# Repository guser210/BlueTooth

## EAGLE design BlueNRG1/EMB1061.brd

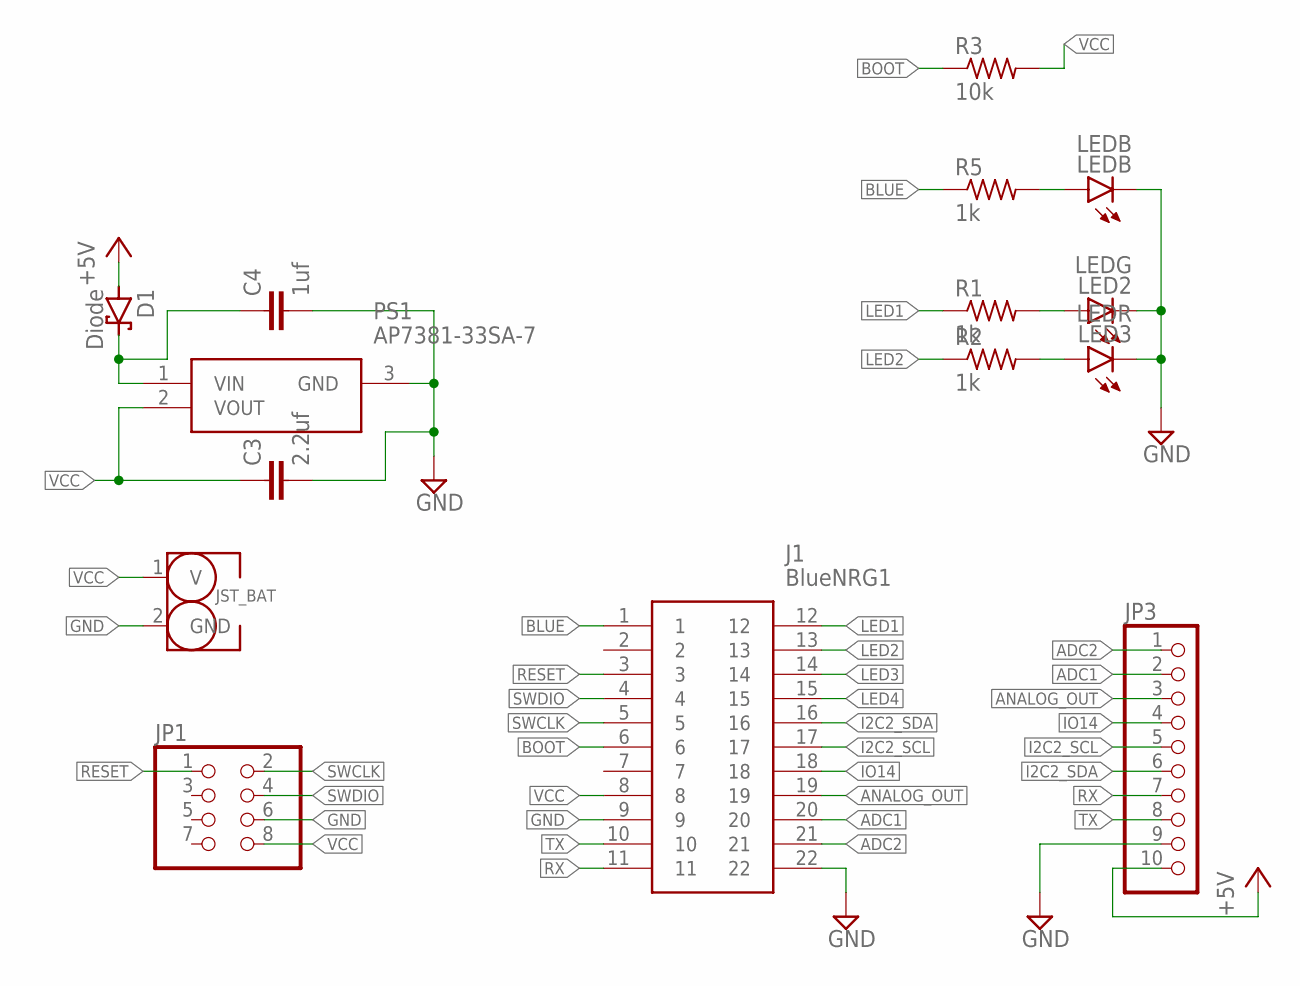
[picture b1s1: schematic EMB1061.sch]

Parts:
C3: 2.2uf; C0603K
C4: 1uf; C0603K
D1: Diode; SOD323_ST
J1: BlueNRG1; 113990637
JP1: PINHD-2X4; 2X04
JP3: PINHD-1X10; 1X10
LED2: LEDG; SML0805
LED3: LEDR; SML0805
LEDB: LEDB; SML0805
PS1: AP7381-33SA-7; SOT96P240X120-3N
R1, R2, R5: 1k; R0805
R3: 10k; R0603
U$1: JST2.0MM_2PIN

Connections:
+5V: D1.A, JP3.10
ADC1: J1.20, JP3.2
ADC2: J1.21, JP3.1
ANALOG_OUT: J1.19, JP3.3
BLUE: J1.1, R5.1
BOOT: J1.6, R3.1
GND: C3.2, C4.2, J1.9, J1.22, JP1.6, JP3.9, LED2.C, LED3.C, LEDB.C, PS1.3 (GND), U$1.2 (GND)
I2C2_SCL: J1.17, JP3.5
I2C2_SDA: J1.16, JP3.6
IO14: J1.18, JP3.4
LED1: J1.12, R1.1
LED2: J1.13, R2.1
LED3: J1.14
LED4: J1.15
unnamed: LEDB.A, R5.2
unnamed: LED2.A, R1.2
unnamed: LED3.A, R2.2
RESET: J1.3, JP1.1
RX: J1.11, JP3.7
SWCLK: J1.5, JP1.2
SWDIO: J1.4, JP1.4
TX: J1.10, JP3.8
VCC: C3.1, J1.8, JP1.8, PS1.2 (VOUT), R3.2, U$1.1 (V)
VIN: C4.1, D1.C, PS1.1 (VIN)

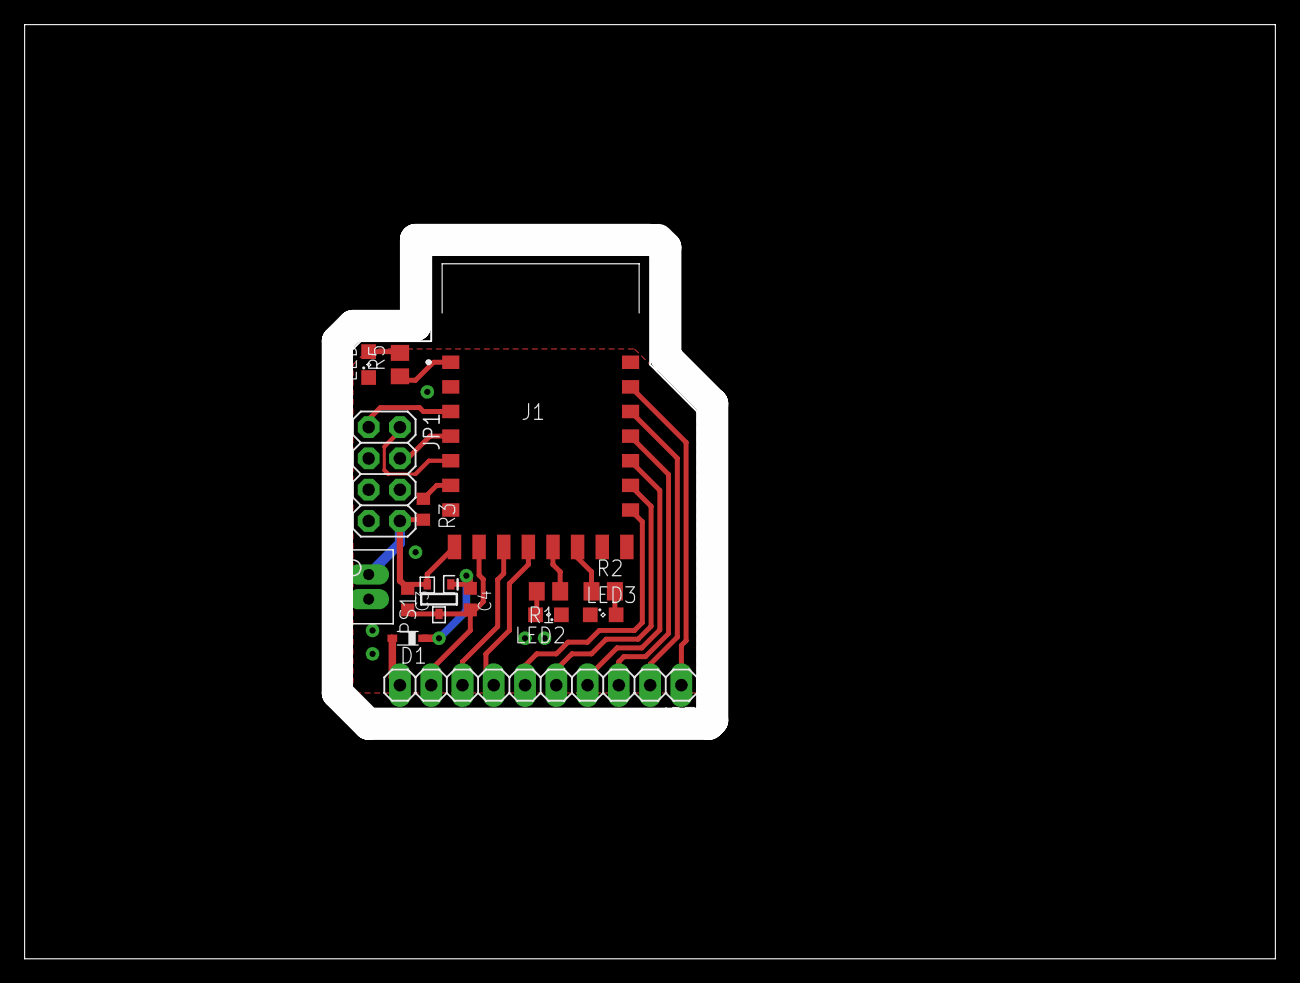
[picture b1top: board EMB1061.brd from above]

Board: 2 copper layers, 99.0 x 73.3 mm, 15 parts (0 on the bottom side), 22 nets.

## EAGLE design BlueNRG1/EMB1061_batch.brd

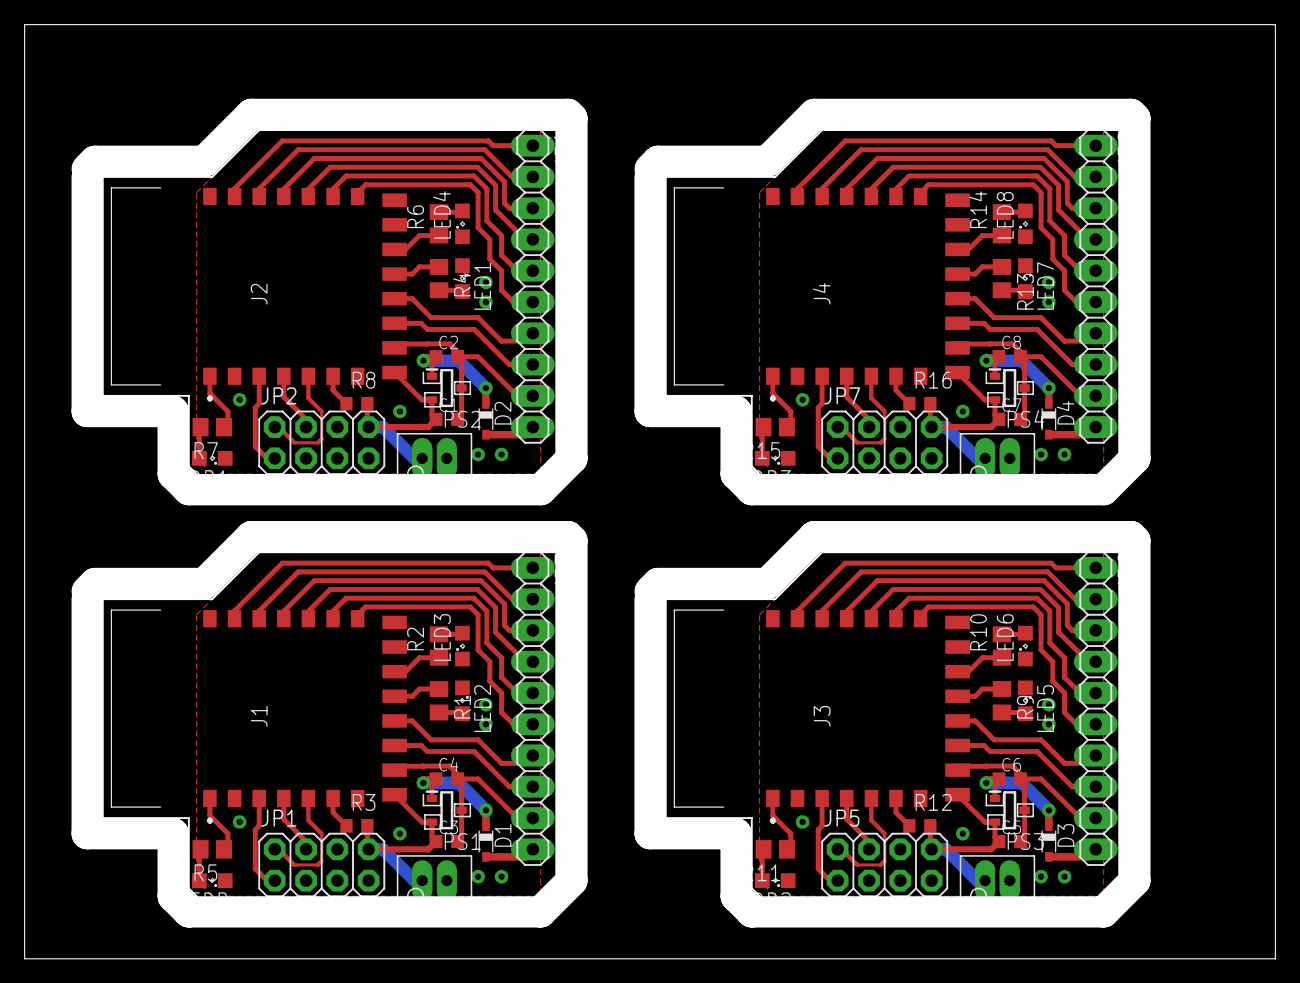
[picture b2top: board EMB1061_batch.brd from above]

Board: 2 copper layers, 99.0 x 73.3 mm, 60 parts (0 on the bottom side), 88 nets.

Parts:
C1, C3, C5, C7: 2.2uf; C0603K
C2, C4, C6, C8: 1uf; C0603K
D1, D2, D3, D4: Diode; SOD323_ST
J1, J2, J3, J4: BlueNRG1; 113990637
JP1, JP2, JP5, JP7: 2X04
JP3, JP4, JP6, JP8: 1X10
LED1, LED2, LED5, LED7: LEDG; SML0805
LED3, LED4, LED6, LED8: LEDR; SML0805
LEDB, LEDB1, LEDB2, LEDB3: LEDB; SML0805
PS1, PS2, PS3, PS4: AP7381-33SA-7; SOT96P240X120-3N
R1, R2, R4, R5, R6, R7, R9, R10, R11, R13, R14, R15: 1k; R0805
R3, R8, R12, R16: 10k; R0603
U$1, U$2, U$3, U$4: JST2.0MM_2PIN

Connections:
+5V: D1.A, JP3.10
+5V1: D2.A, JP4.10
+5V2: D3.A, JP6.10
+5V3: D4.A, JP8.10
ADC1: J1.20, JP3.2
ADC2: J1.21, JP3.1
ADC3: J2.20, JP4.2
ADC4: J2.21, JP4.1
ADC5: J3.20, JP6.2
ADC6: J3.21, JP6.1
ADC7: J4.20, JP8.2
ADC8: J4.21, JP8.1
ANALOG_OUT: J1.19, JP3.3
ANALOG_OUT1: J2.19, JP4.3
ANALOG_OUT2: J3.19, JP6.3
ANALOG_OUT3: J4.19, JP8.3
BLUE: J1.1, R5.1
BLUE1: J2.1, R7.1
BLUE2: J3.1, R11.1
BLUE3: J4.1, R15.1
BOOT: J1.6, R3.1
BOOT1: J2.6, R8.1
BOOT2: J3.6, R12.1
BOOT3: J4.6, R16.1
GND: C3.2, C4.2, J1.9, J1.22, JP1.6, JP3.9, LED2.C, LED3.C, LEDB.C, PS1.3, U$1.2
GND1: C1.2, C2.2, J2.9, J2.22, JP2.6, JP4.9, LED1.C, LED4.C, LEDB1.C, PS2.3, U$2.2
GND2: C5.2, C6.2, J3.9, J3.22, JP5.6, JP6.9, LED5.C, LED6.C, LEDB2.C, PS3.3, U$3.2
GND3: C7.2, C8.2, J4.9, J4.22, JP7.6, JP8.9, LED7.C, LED8.C, LEDB3.C, PS4.3, U$4.2
I2C2_SCL: J1.17, JP3.5
I2C2_SCL1: J2.17, JP4.5
I2C2_SCL2: J3.17, JP6.5
I2C2_SCL3: J4.17, JP8.5
I2C2_SDA: J1.16, JP3.6
I2C2_SDA1: J2.16, JP4.6
I2C2_SDA2: J3.16, JP6.6
I2C2_SDA3: J4.16, JP8.6
IO1: J2.18, JP4.4
IO2: J3.18, JP6.4
IO3: J4.18, JP8.4
IO14: J1.18, JP3.4
LED1: J1.12, R1.1
LED2: J1.13, R2.1
LED5: J2.12, R4.1
LED6: J2.13, R6.1
LED9: J3.12, R9.1
LED10: J3.13, R10.1
LED13: J4.12, R13.1
LED14: J4.13, R14.1
unnamed: LEDB.A, R5.2
unnamed: LED1.A, R4.2
unnamed: LED4.A, R6.2
unnamed: LEDB1.A, R7.2
unnamed: LED5.A, R9.2
unnamed: LED6.A, R10.2
unnamed: LEDB2.A, R11.2
unnamed: LED7.A, R13.2
unnamed: LED8.A, R14.2
unnamed: LEDB3.A, R15.2
unnamed: LED2.A, R1.2
unnamed: LED3.A, R2.2
RESET: J1.3, JP1.1
RESET1: J2.3, JP2.1
RESET2: J3.3, JP5.1
RESET3: J4.3, JP7.1
RX: J1.11, JP3.7
RX1: J2.11, JP4.7
RX2: J3.11, JP6.7
RX3: J4.11, JP8.7
SWCLK: J1.5, JP1.2
SWCLK1: J2.5, JP2.2
SWCLK2: J3.5, JP5.2
SWCLK3: J4.5, JP7.2
SWDIO: J1.4, JP1.4
SWDIO1: J2.4, JP2.4
SWDIO2: J3.4, JP5.4
SWDIO3: J4.4, JP7.4
TX: J1.10, JP3.8
TX1: J2.10, JP4.8
TX2: J3.10, JP6.8
TX3: J4.10, JP8.8
VCC: C3.1, J1.8, JP1.8, PS1.2, R3.2, U$1.1
VCC1: C1.1, J2.8, JP2.8, PS2.2, R8.2, U$2.1
VCC2: C5.1, J3.8, JP5.8, PS3.2, R12.2, U$3.1
VCC3: C7.1, J4.8, JP7.8, PS4.2, R16.2, U$4.1
VIN: C4.1, D1.C, PS1.1
VIN1: C2.1, D2.C, PS2.1
VIN2: C6.1, D3.C, PS3.1
VIN3: C8.1, D4.C, PS4.1
